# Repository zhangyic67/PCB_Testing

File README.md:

# PCB_Testing

This is a PCB project using KiCAD with STmicrocontroller

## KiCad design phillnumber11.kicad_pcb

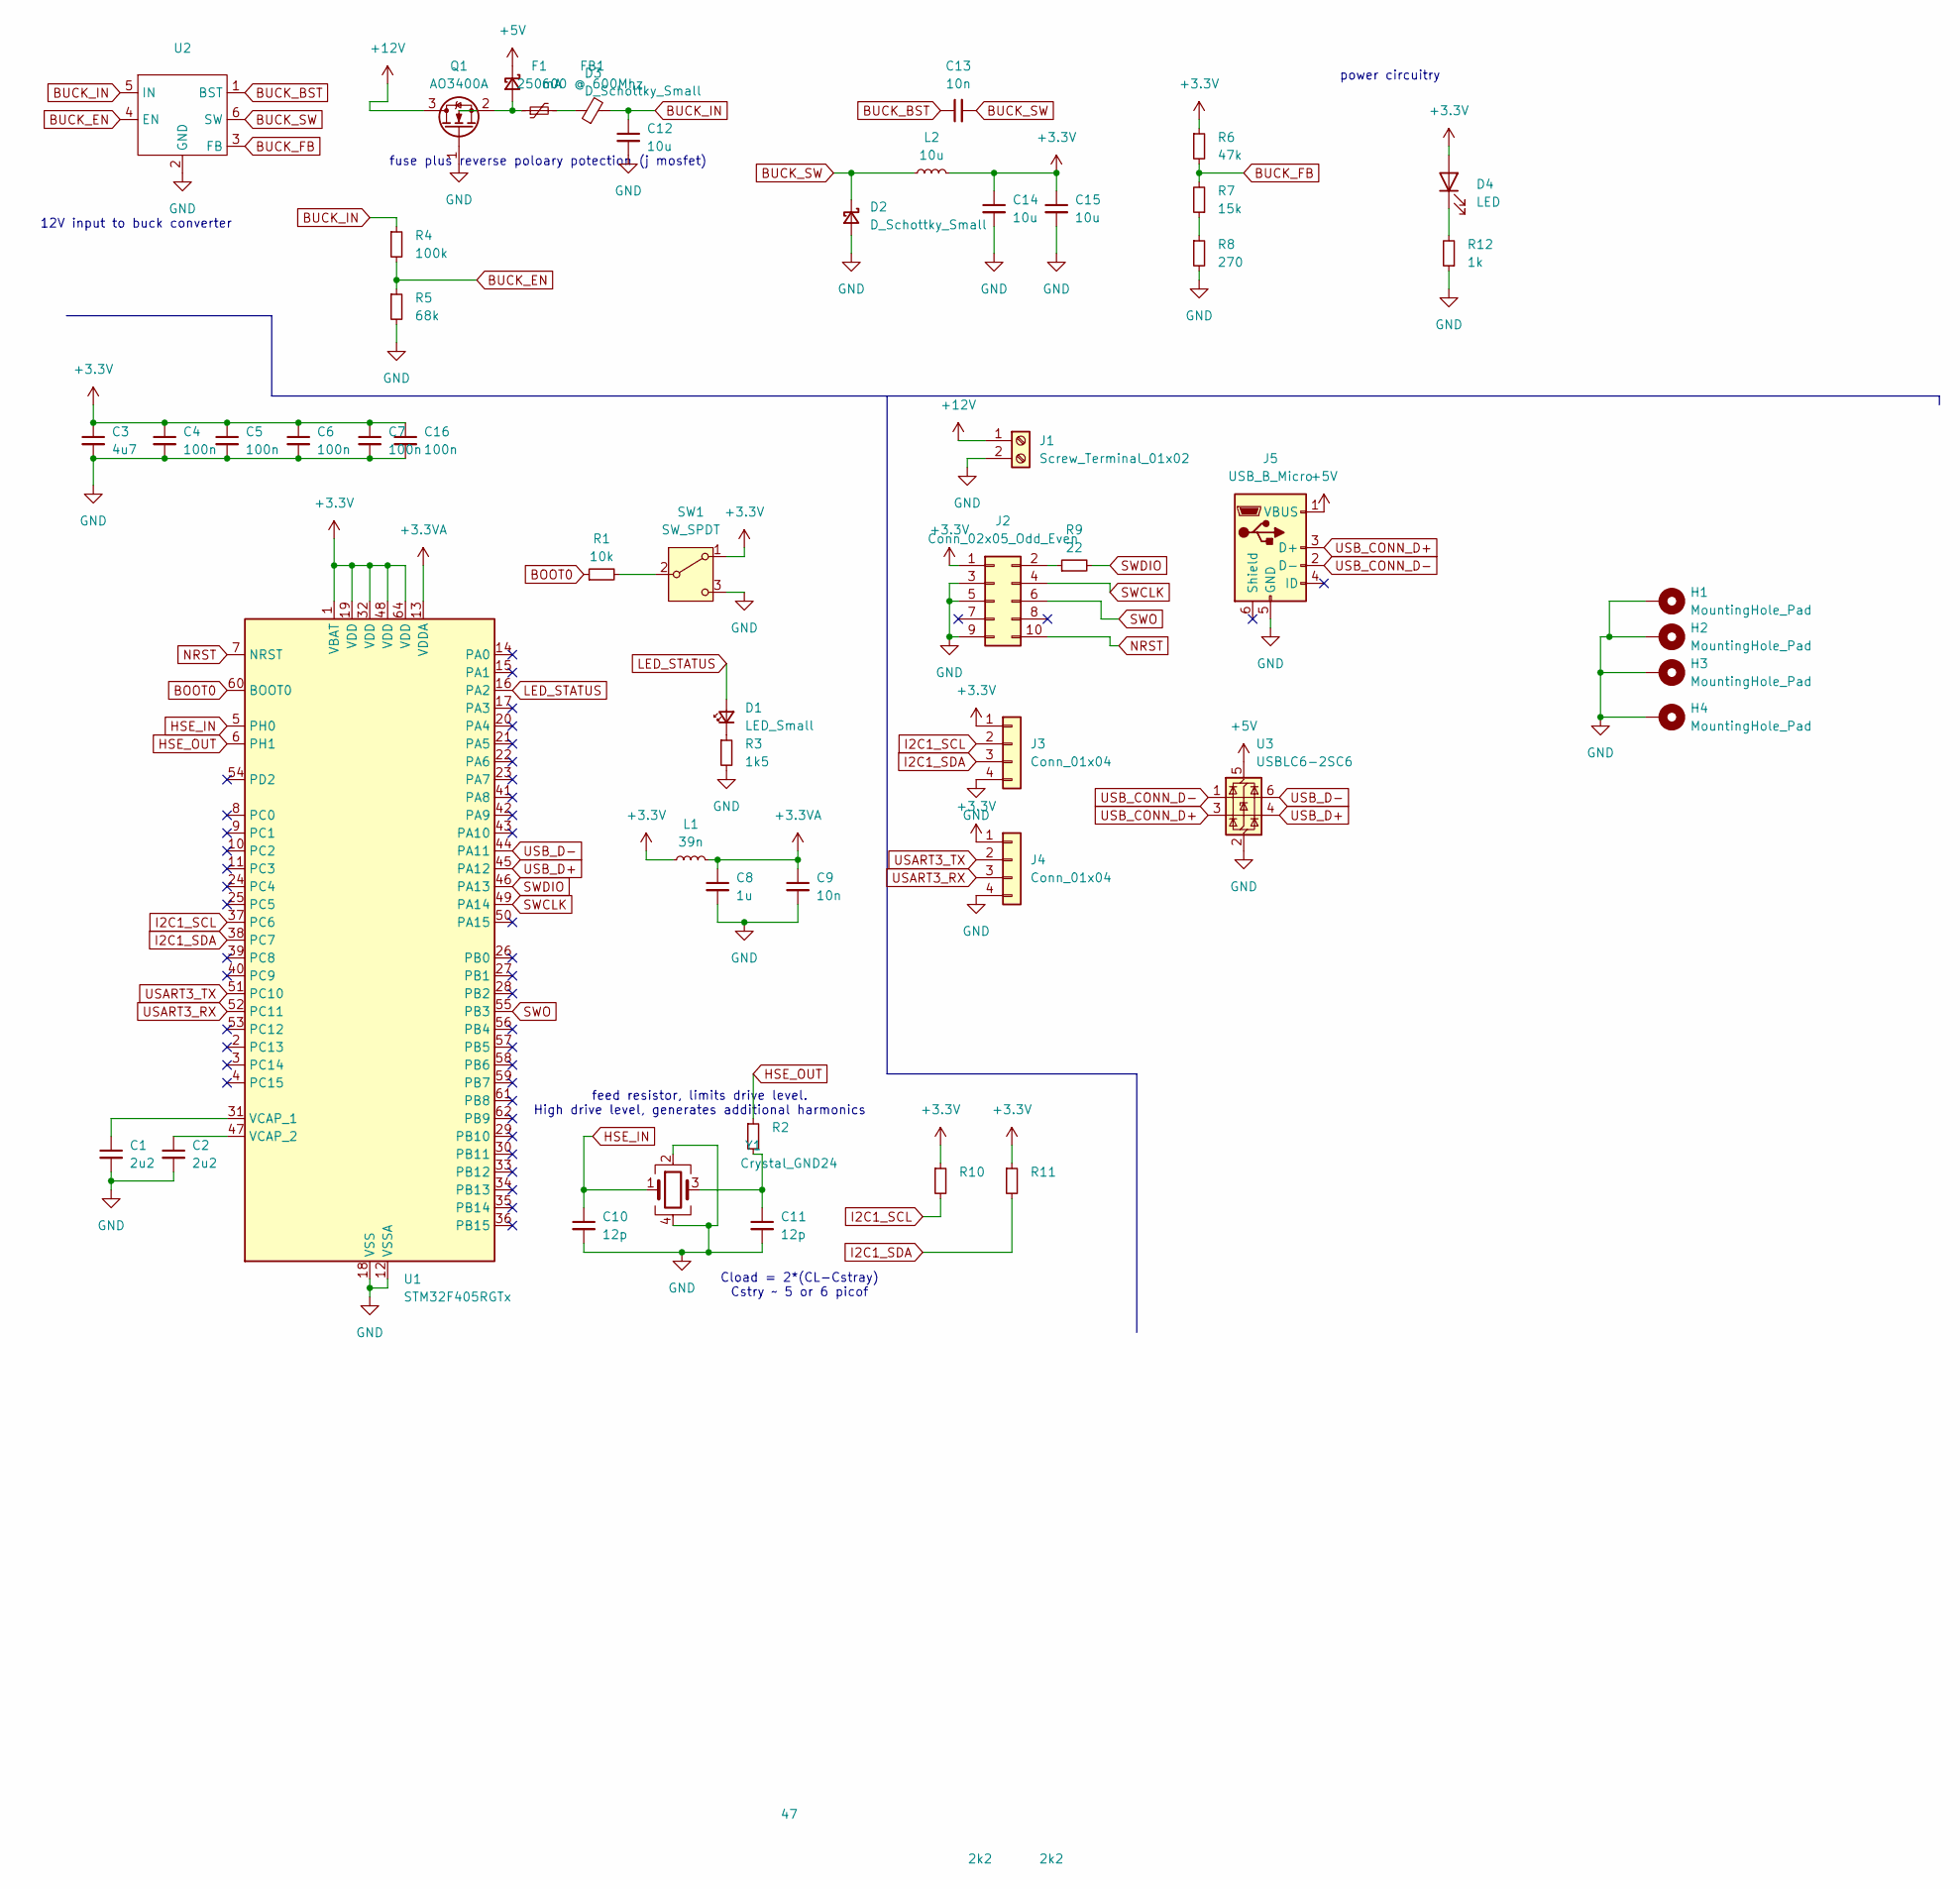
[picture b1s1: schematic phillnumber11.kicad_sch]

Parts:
C1, C2: 2u2; C_0603_1608Metric
C3: 4u7; C_0603_1608Metric
C4, C5, C6, C7, C16: 100n; C_0402_1005Metric
C8: 1u; C_0402_1005Metric
C9: 10n; C_0402_1005Metric
C10, C11: 12p; C_0402_1005Metric
C12, C14, C15: 10u; C_1206_3216Metric
C13: 10n; C_0603_1608Metric
D1: LED_Small; LED_0603_1608Metric
D2, D3: D_Schottky_Small; D_SOD-123
D4: LED; LED_0603_1608Metric
F1: 250mA; Fuse_1206_3216Metric
FB1: 600 @ 600Mhz; L_0805_2012Metric
H1, H2, H3, H4: MountingHole_Pad; MountingHole_4.3mm_M4_Pad_Via
J1: Screw_Terminal_01x02; TerminalBlock_Phoenix_PT-1,5-2-3.5-H_1x02_P3.50mm_Horizontal
J2: Conn_02x05_Odd_Even; PinSocket_2x05_P1.27mm_Vertical_SMD
J3, J4: Conn_01x04; Molex_PicoBlade_53048-0410_1x04_P1.25mm_Horizontal
J5: USB_B_Micro; USB3_A_Molex_48393-001
L1: 39n; L_0402_1005Metric
L2: 10u; L_Sunlord_MWSA0518S
Q1: AO3400A; SOT-23
R1: 10k; R_0402_1005Metric
R2: 47; R_0402_1005Metric
R3: 1k5; R_0603_1608Metric
R4: 100k; R_0603_1608Metric
R5: 68k; R_0603_1608Metric
R6: 47k; R_0603_1608Metric
R7: 15k; R_0603_1608Metric
R8: 270; R_0603_1608Metric
R9: 22; R_0402_1005Metric
R10, R11: 2k2; R_0402_1005Metric
R12: 1k; R_0603_1608Metric
SW1: SW_SPDT; SW_SPDT_PCM12
U1: STM32F405RGTx; LQFP-64_10x10mm_P0.5mm
U2: SOT-23-6
U3: USBLC6-2SC6; SOT-23-6
Y1: Crystal_GND24; Crystal_SMD_3225-4Pin_3.2x2.5mm

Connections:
+3.3V: C3.1, C4.1, C5.1, C6.1, C7.1, C14.1, C15.1, C16.1, D4.2 (A), J2.1, J3.1, J4.1, L1.1, L2.2, R6.1, R10.1, R11.1, SW1.1 (A), U1.1 (VBAT), U1.19 (VDD), U1.32 (VDD), U1.48 (VDD), U1.64 (VDD)
+3.3VA: C8.1, C9.1, L1.2, U1.13 (VDDA)
+5V: D3.1 (K), J5.1 (VBUS), U3.5 (VBUS)
+12V: J1.1, Q1.3 (D)
BOOT0: R1.1, U1.60 (BOOT0)
BUCK_BST: C13.1, U2.1 (BST)
BUCK_EN: R4.2, R5.1, U2.4 (EN)
BUCK_FB: R6.2, R7.2, U2.3 (FB)
BUCK_IN: C12.1, FB1.2, R4.1, U2.5 (IN)
BUCK_SW: C13.2, D2.1 (K), L2.1, U2.6 (SW)
GND: C1.2, C2.2, C3.2, C4.2, C5.2, C6.2, C7.2, C8.2, C9.2, C10.2, C11.2, C12.2, C14.2, C15.2, C16.2, D2.2 (A), H1.1, H2.1, H3.1, H4.1, J1.2, J2.3, J2.5, J2.9, J3.4, J4.4, J5.5 (GND), Q1.1 (G), R3.2, R5.2, R8.2, R12.1, SW1.3 (C), U1.12 (VSSA), U1.18 (VSS), U1.63 (VSS), U2.2 (GND), U3.2 (GND), Y1.2, Y1.4
HSE_IN: C10.1, U1.5 (PH0), Y1.1
HSE_OUT: R2.1, U1.6 (PH1)
I2C1_SCL: J3.2, R10.2, U1.37 (PC6)
I2C1_SDA: J3.3, R11.2, U1.38 (PC7)
LED_STATUS: D1.2 (A), U1.16 (PA2)
NRST: J2.10, U1.7 (NRST)
unnamed: C11.1, R2.2, Y1.3
unnamed: D1.1 (K), R3.1
unnamed: D3.2 (A), F1.1, Q1.2 (S)
unnamed: D4.1 (K), R12.2
unnamed: F1.2, FB1.1
unnamed: J2.2, R9.1
unnamed: R7.1, R8.1
unnamed: R1.2, SW1.2 (B)
unnamed: C1.1, U1.31 (VCAP_1)
unnamed: C2.1, U1.47 (VCAP_2)
SWCLK: J2.4, U1.49 (PA14)
SWDIO: R9.2, U1.46 (PA13)
SWO: J2.6, U1.55 (PB3)
USART3_RX: J4.3, U1.52 (PC11)
USART3_TX: J4.2, U1.51 (PC10)
USB_CONN_D+: J5.3 (D+), U3.3 (I/O2)
USB_CONN_D-: J5.2 (D-), U3.1 (I/O1)
USB_D+: U1.45 (PA12), U3.4 (I/O2)
USB_D-: U1.44 (PA11), U3.6 (I/O1)

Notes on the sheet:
feed resistor, limits drive level. High drive level, generates additional harmonics
12V input to buck converter
Cload = 2*(CL-Cstray) Cstry ~ 5 or 6 picof
fuse plus reverse poloary potection (j mosfet)
power circuitry

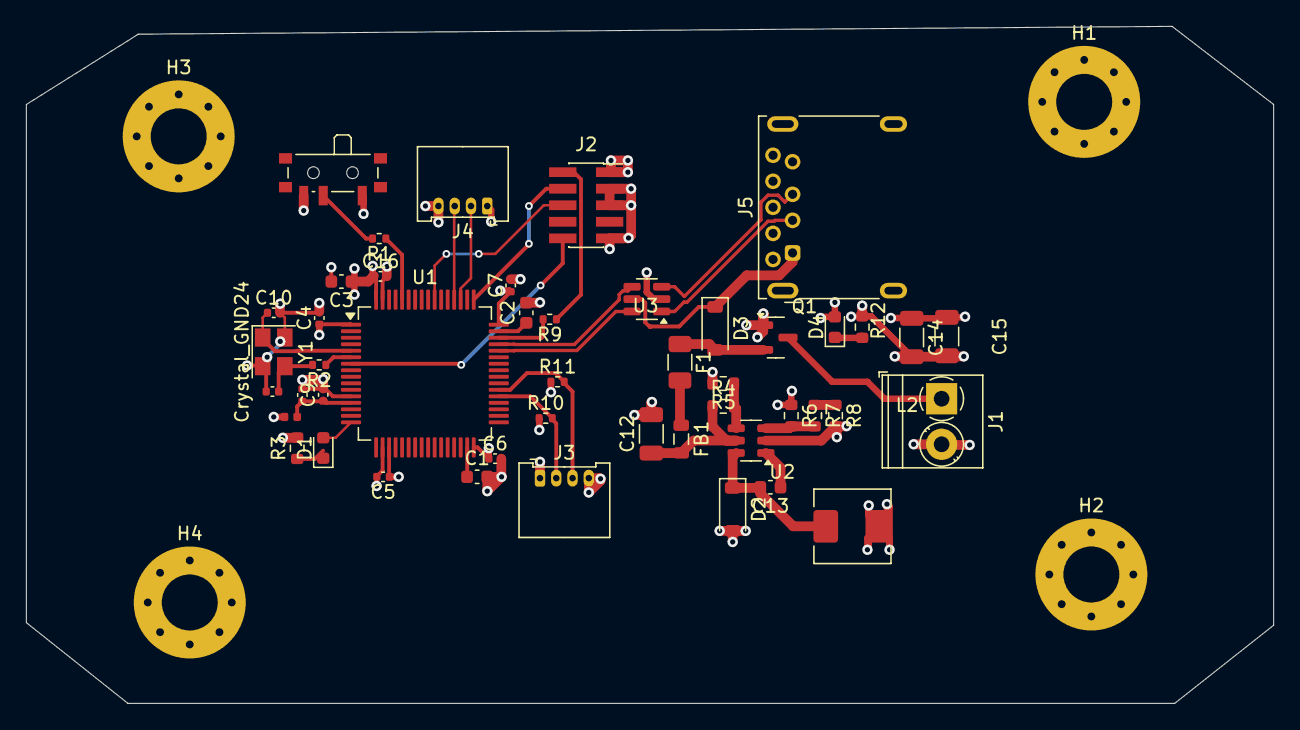
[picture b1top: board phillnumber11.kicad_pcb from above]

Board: 4 copper layers, 95.8 x 52.0 mm, 51 parts (0 on the bottom side), 36 nets.

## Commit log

2025-05-21 Add pcb and chematic files
